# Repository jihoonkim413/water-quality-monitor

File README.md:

# Water Quality Monitor

ESP32 DevKit V1 + DWS-MH-02 water sensor (flow, temperature, TDS) → home server → phone app.

```
[sensor] --> [ESP32: firmware/] --WiFi, HTTP POST--> [home server: server/app.py + SQLite] <-- [phone app]
```

## 1. Parts

| Part | Use |
|---|---|
| ESP32 DevKit V1 | reads the sensor, sends over WiFi |
| 4.7 kΩ resistor | TDS reference |
| 10 kΩ resistor | temperature divider |
| 10 kΩ + 20 kΩ resistors | drop the 5 V flow pulse to ~3.3 V |
| 100 nF capacitor (optional) | smooths the temperature reading |

No ADC or TDS board needed: the ESP32 has analog inputs, and it drives the TDS electrodes
itself with alternating polarity (plain DC would corrode them).

## 2. Identify the wires first

Colors vary between batches. Check with a multimeter before wiring:

- **TDS pair**: open circuit when dry, some resistance when both are in water.
- **Temperature**: about 10 kΩ to the − wire at room temperature (NTC thermistor).
  If yours differs, change `NTC_R25` in [firmware/src/main.cpp](firmware/src/main.cpp).
- **Pulse**: power the sensor (+5 V / GND), measure the pulse wire while you blow through it.
  - Switches 0 V ↔ ~5 V: use the divider below.
  - Stays at 0 V: it's open-collector. Skip the divider, wire it straight to GPIO27, and change
    `pinMode(PIN_FLOW, INPUT)` to `INPUT_PULLUP`.

Typical colors: red = +5 V, black = GND, yellow = pulse, green = temperature, blue + other wire = TDS.

## 3. Wiring

Full schematic: https://claude.ai/artifact/Ly4EsdJo9hSQuPKV1TVnU7

```
Sensor +5V (red)    -> ESP32 VIN   (5 V from USB)
Sensor GND (black)  -> ESP32 GND

Pulse (yellow) --[10k]--+-- GPIO27 (D27)
                        |
                      [20k]
                        |
                       GND

3V3 --[10k]--+-- GPIO34 (D34)
             |
      Temperature (green)        (thermistor's other end is sensor GND)
             |
          [100nF] to GND (optional)

GPIO25 (D25) --[4.7k]--+-- GPIO35 (D35)
                       |
                 TDS electrode 1

GPIO26 (D26) ---------- TDS electrode 2
```

Never connect a 5 V signal straight to an ESP32 pin.

## 4. Home server

Any always-on machine on your network. Your Pi 3 works well for this.

```bash
cd server
python3 -m venv .venv && . .venv/bin/activate
pip install -r requirements.txt
WATER_API_KEY=pick-a-long-random-string uvicorn app:app --host 0.0.0.0 --port 8000
```

Run at boot on a Pi: edit the key in `water-server.service`, then

```bash
sudo cp water-server.service /etc/systemd/system/
sudo systemctl enable --now water-server
```

Open `http://<server-ip>:8000/docs` to try the API.

| Endpoint | Returns |
|---|---|
| `POST /api/readings` | stores a list of readings (used by the ESP32) |
| `GET /api/readings/latest` | newest reading |
| `GET /api/readings?hours=24` | history for charts |
| `GET /api/usage?days=7` | liters per day |
| `GET /api/health` | `{"ok": true}` |

All endpoints except `/api/health` need the header `X-API-Key: <your key>`.

## 5. Flash the ESP32

Install [PlatformIO](https://platformio.org) (the VS Code extension is easiest), then:

1. Copy `firmware/include/secrets.example.h` to `secrets.h` and fill in WiFi, server URL, API key
   and an `OTA_PASS` of your choice.
2. Plug in the board and run `pio run -e esp32dev -t upload` in `firmware/`
   (some DevKit V1 boards need the **BOOT** button held when "Connecting..." appears).
3. Run `pio device monitor` to watch readings every 10 s.

### Updates over WiFi

After the first USB flash, the board accepts new firmware over WiFi:

1. Copy `firmware/local.example.ini` to `local.ini`. Set `upload_port` to `<DEVICE_ID>.local`
   (or the board's IP) and `--auth=` to the same `OTA_PASS` as in `secrets.h`.
2. Run `pio run -e ota -t upload` in `firmware/`. It takes about 2–3 minutes, then the board reboots.

If a WiFi update leaves the board unable to reach WiFi (bad credentials, a crash at boot),
flash it once more over USB. Changing `board_build.partitions` also needs a USB flash.

## 6. Calibration

Type these in the serial monitor (USB, 115200 baud), or over WiFi once the board is on the network:

```
nc kitchen-filter.local 23     # your DEVICE_ID, or the board's IP
```

Send your `OTA_PASS` as the first line, then any command below. `bye` disconnects.

| Command | What to do |
|---|---|
| `flowstart` → pour exactly 1 L → `flowstop` | saves pulses per liter |
| `rs 748` | probe series resistance in ohms (see below); set it before `tds` |
| `tds 342` | probe in a 342 ppm calibration solution (or any water you measured with a TDS pen; use that number) |
| `status` | prints temperature, water resistance and TDS now |

Calibration is saved on the ESP32 and survives reboots and reflashing.
`tds` refuses to run if the temperature reading is missing or outside 1–45 °C, because the
temperature at calibration time is built into every later TDS value. Fix the temperature first.
For temperature, compare with a thermometer and adjust `NTC_BETA` (3435 and 3950 are common).

**Series resistance (`rs`).** The DWS-MH-02 probe reads as the water plus about 750 Ω in series.
With `rs 0`, a calibration in filtered water makes tap water read about half of what a pen says.
To measure it for your probe, note the `water ... ohm` value from `status` and a pen reading in
two or three waters (filtered, tap, and a 50/50 mix), then pick `rs` so that
`ppm × (ohms − rs)` is about the same for all of them (correct ohms to 25 °C first:
`ohms × (1 + 0.02 × (temp − 25))`). Our probe: filtered 11.5 ppm / 42.6k, 50/50 335 ppm / 2.24k,
tap 582 ppm / 1.57k → `rs 748`, within ±2.5% across all three.

TDS accuracy is roughly ±5% after calibration — good for trends and filter-change alerts.
The firmware picks the 4.7k or 47k reference automatically, so the `ref` in `status` shows which one it used.

## 7. Phone access

- **At home**: the app calls `http://<server-ip>:8000/api/...`.
- **Away from home**: install [Tailscale](https://tailscale.com) on the server and phone and use the
  server's Tailscale address. Don't port-forward this server to the internet — it has no HTTPS.

If the server is down, the ESP32 keeps up to ~2.7 hours of readings in memory and sends them later.

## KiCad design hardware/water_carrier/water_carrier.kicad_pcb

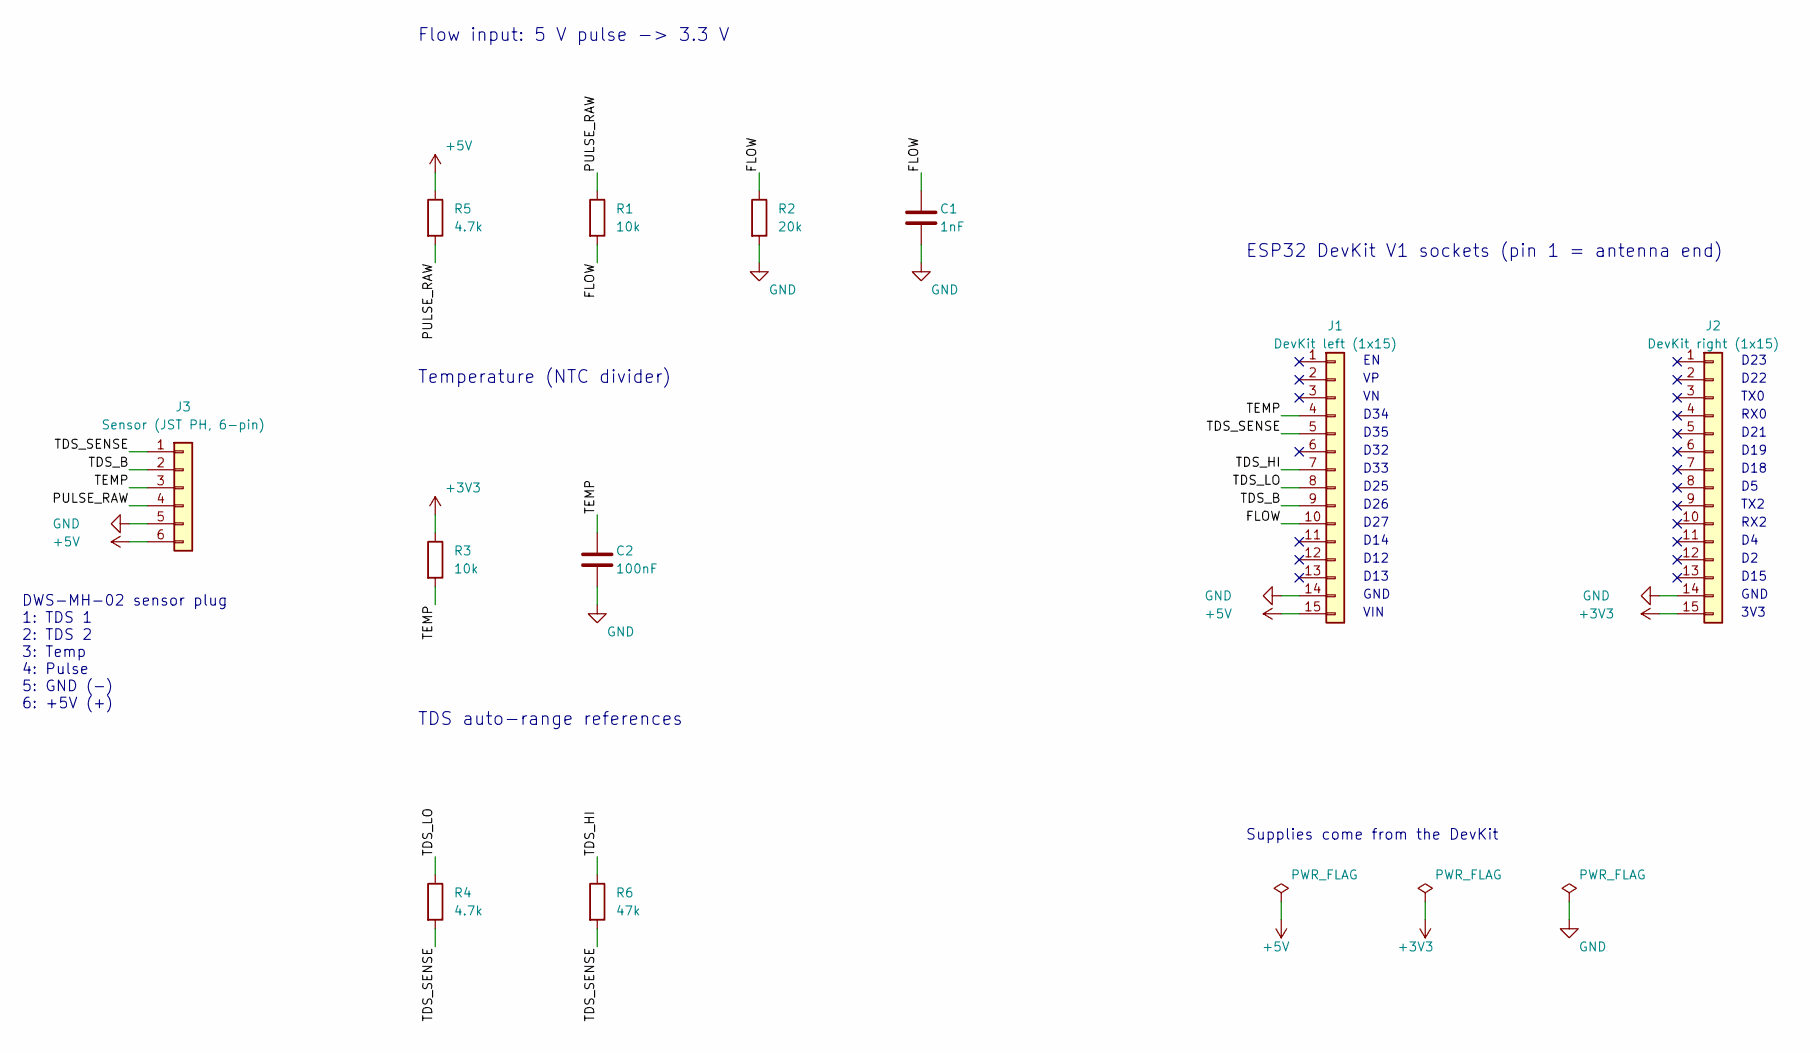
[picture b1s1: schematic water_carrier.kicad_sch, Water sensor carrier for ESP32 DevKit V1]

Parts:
C1: 1nF; C_0805_2012Metric; LCSC C46653
C2: 100nF; C_0805_2012Metric; LCSC C49678
J1: DevKit left (1x15); PinSocket_1x15_P2.54mm_Vertical
J2: DevKit right (1x15); PinSocket_1x15_P2.54mm_Vertical
J3: Sensor (JST PH, 6-pin); JST_PH_B6B-PH-K_1x06_P2.00mm_Vertical
R1, R3: 10k; R_0805_2012Metric; LCSC C17414
R2: 20k; R_0805_2012Metric; LCSC C4328
R4, R5: 4.7k; R_0805_2012Metric; LCSC C17673
R6: 47k; R_0805_2012Metric; LCSC C17713

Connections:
+3V3: J2.15, R3.1
+5V: J1.15, J3.6, R5.1
/FLOW: C1.1, J1.10, R1.2, R2.1
/PULSE_RAW: J3.4, R1.1, R5.2
/TDS_B: J1.9, J3.2
/TDS_HI: J1.7, R6.1
/TDS_LO: J1.8, R4.1
/TDS_SENSE: J1.5, J3.1, R4.2, R6.2
/TEMP: C2.1, J1.4, J3.3, R3.2
GND: C1.2, C2.2, J1.14, J2.14, J3.5, R2.2

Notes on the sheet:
DWS-MH-02 sensor plug 1: TDS 1 2: TDS 2 3: Temp 4: Pulse 5: GND (-) 6: +5V (+)
D34
D35
D32
D33
D25
D26
D27
D14
D12
D13
GND
VIN
D23
D22
TX0
RX0
D21
D19
D18
TX2
RX2
D15
3V3
ESP32 DevKit V1 sockets (pin 1 = antenna end)
Flow input: 5 V pulse -> 3.3 V
Temperature (NTC divider)
TDS auto-range references
Supplies come from the DevKit

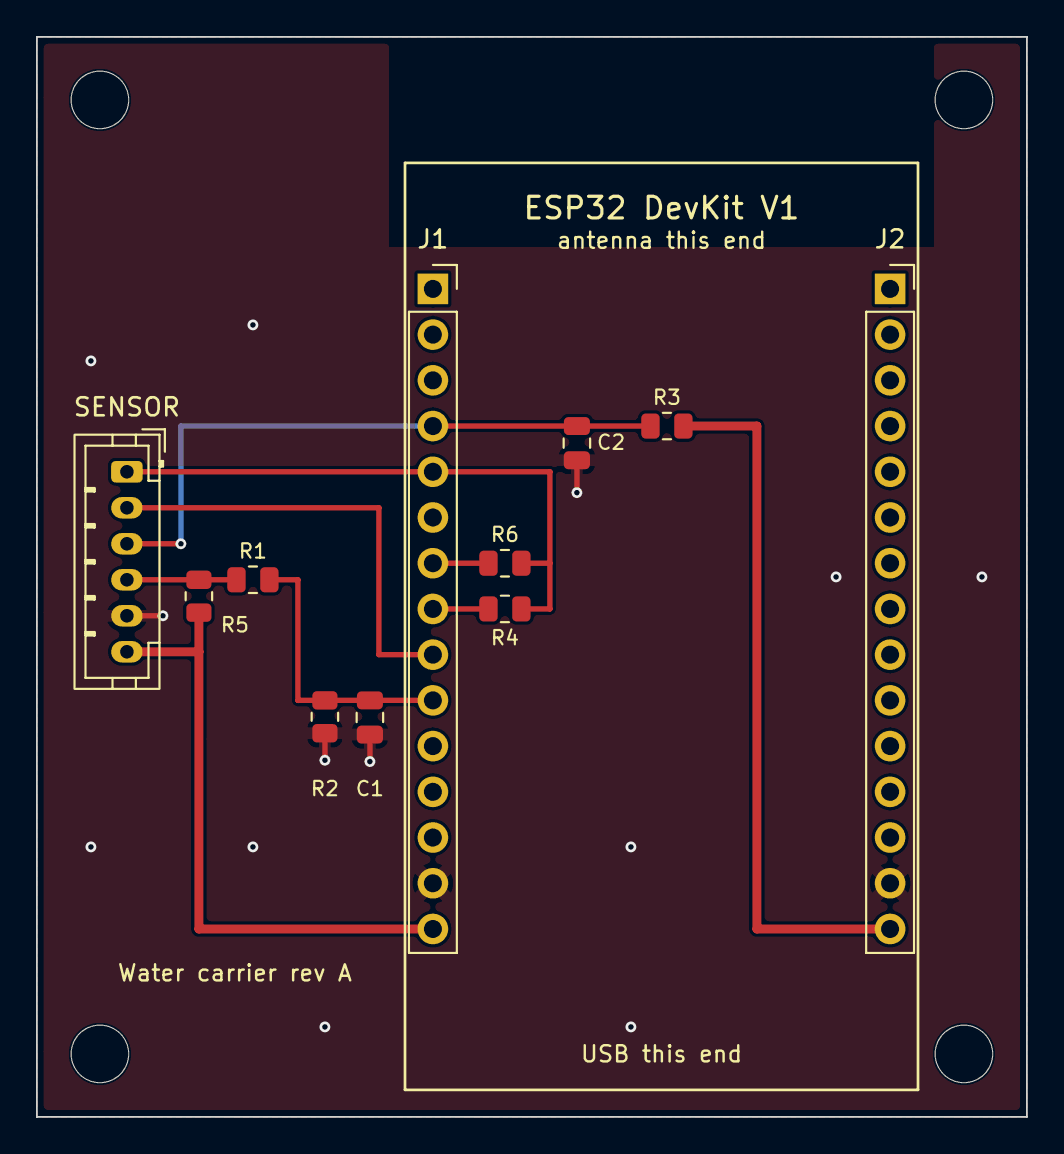
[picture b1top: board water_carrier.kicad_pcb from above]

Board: 2 copper layers, 55.0 x 60.0 mm, 15 parts (0 on the bottom side), 10 nets.

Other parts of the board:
H1, H2, H3, H4: M3; MountingHole_3.2mm_M3

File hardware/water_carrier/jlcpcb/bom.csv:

Comment,Designator,Footprint,LCSC Part #
1nF,C1,C_0805_2012Metric,C46653
100nF,C2,C_0805_2012Metric,C49678
10k,"R1,R3",R_0805_2012Metric,C17414
20k,R2,R_0805_2012Metric,C4328
4.7k,"R4,R5",R_0805_2012Metric,C17673
47k,R6,R_0805_2012Metric,C17713

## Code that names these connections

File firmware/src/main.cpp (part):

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#include "secrets.h"

// ------------------------------------------------------------------ pins --
constexpr int PIN_FLOW      = 27;  // flow pulse, through 10k/20k divider
constexpr int PIN_TDS_LO    = 25;  // TDS drive, through R_REF_LO to the sense node
constexpr int PIN_TDS_HI    = 33;  // TDS drive, through R_REF_HI to the sense node (optional)
constexpr int PIN_TDS_B     = 26;  // TDS drive, straight to the second electrode
constexpr int PIN_TDS_SENSE = 35;  // ADC1: sense node, also the first electrode
constexpr int PIN_TEMP      = 34;  // ADC1: node between 10k pull-up and thermistor

// --------------------------------------------------------------- circuit --
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  int good = 0;
  for (int i = 0; i < CYCLES; i++) {
    digitalWrite(drivePin, HIGH);
    digitalWrite(PIN_TDS_B, LOW);
    delayMicroseconds(10);
    float vf = analogReadMilliVolts(PIN_TDS_SENSE) / 1000.0f;

    digitalWrite(drivePin, LOW);
    digitalWrite(PIN_TDS_B, HIGH);
    delayMicroseconds(10);
    float vr = analogReadMilliVolts(PIN_TDS_SENSE) / 1000.0f;

    // forward: V -> rRef -> node -> water -> 0V, so vf = V * Rw / (Rw + rRef)
    // reverse: V -> water -> node -> rRef -> 0V, so vr = V * rRef / (Rw + rRef)
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    }
  }
  digitalWrite(drivePin, LOW);
  digitalWrite(PIN_TDS_B, LOW);
  lastVf = sumVf / CYCLES;
  lastVr = sumVr / CYCLES;
  lastRef = rRef;
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// Auto-range: try 4.7k first; for high-resistance (low-ppm) water switch to
// 47k. If the 47k resistor isn't fitted, that reading fails and 4.7k is kept.
float readWaterOhms() {
  float r = measureOhms(PIN_TDS_LO, PIN_TDS_HI, R_REF_LO);
  if (isinf(r) || r > RANGE_SWITCH) {
    float vf = lastVf, vr = lastVr;
    float rHi = measureOhms(PIN_TDS_HI, PIN_TDS_LO, R_REF_HI);
    if (!isinf(rHi)) return rHi;
    lastVf = vf; lastVr = vr; lastRef = R_REF_LO;
  }
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  seriesOhms = prefs.getFloat("rs", 0.0f);
  pulsesPerLiter = prefs.getFloat("ppl", 450.0f);  // placeholder until calibrated

  pinMode(PIN_TDS_LO, OUTPUT);
  pinMode(PIN_TDS_HI, INPUT);
  pinMode(PIN_TDS_B, OUTPUT);
  digitalWrite(PIN_TDS_LO, LOW);
  digitalWrite(PIN_TDS_B, LOW);
  analogSetPinAttenuation(PIN_TDS_SENSE, ADC_11db);
  analogSetPinAttenuation(PIN_TEMP, ADC_11db);

  pinMode(PIN_FLOW, INPUT);
  attachInterrupt(digitalPinToInterrupt(PIN_FLOW), onPulse, RISING);

  WiFi.mode(WIFI_STA);
  WiFi.setAutoReconnect(true);
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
